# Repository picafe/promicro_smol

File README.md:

# promicro_smol

`promicro_smol` is a compact shield PCB for the nRF52840 Supermini/Pro Micro used in DIY SlimeVR trackers. It has an IMU, magnetometer, two buttons, RGB LED, battery pads and voltage reading functionality. It is designed to be compatible with existing Chrysalis enclosures (not yet verified). Production files can be found in `/pcb/production/`.

## Why I Made This

This project started as a modification of Chrysalis to support operation at 1.8V logic and to add a few features. The main changes were to make the magnetometer support 1.8V logic, switch to a MOSFET-controlled RGB LED, add a battery voltage divider for better capacity measurement, and to make sure SWD pads are accessible through a board cutout. I made these changes ensuring the board is optimized for JLCPCB economic assembly.

## Pictures

### Schematic
[View Online](https://kicanvas.org/?repo=https%3A%2F%2Fgithub.com%2Fpicafe%2Fpromicro_smol%2Fblob%2Fmain%2Fpcb%2Fpromicro_smol.kicad_sch)

### PCB
[View Online](https://kicanvas.org/?repo=https%3A%2F%2Fgithub.com%2Fpicafe%2Fpromicro_smol%2Fblob%2Fmain%2Fpcb%2Fpromicro_smol.kicad_pcb)

## Credits and Attribution

This work is derived from the [kounocom/Chrysalis](https://github.com/kounocom/Chrysalis) hardware project.

Files from `/pcb/Chrysalis-Footprints.pretty` are sourced from the Chrysalis project with and without modifications.

The upstream project is provided under CERN-OHL-S-2.0, and this repository includes the applicable license text in `LICENSE.md`.

## Bill of Materials

LCSC and other supplier pricing moves with stock, demand, quantity, and exchange rates. Treat **Unit cost** and **Total cost** as a very rough estimate. For example, the LSM6DSV has increased in price significantly in the past few months due to shortages and decreasing stock.

| Item         | Value / Part                                                                                                                                                                                                                                                                                                                          | Quantity | Unit cost | Total cost |
| ------------ | ------------------------------------------------------------------------------------------------------------------------------------------------------------------------------------------------------------------------------------------------------------------------------------------------------------------------------------- | -------- | --------- | ---------- |
| MCU module   | ProMicro nRF52840 (can be found on Aliexpress)                                                                                                                                                                                                                                                                                        | 1        | $3          | $3          |
| IMU          | [LSM6DSVQTR (C17496470)](https://www.lcsc.com/product-detail/C17496470.html)                                                                                                                                                                                                                                                             | 1        | $2.27          | $2.27          |
| Magnetometer | [QMC6309 (C5439871)](https://www.lcsc.com/product-detail/C5439871.html)                                                                                                                                                                                                                                                               | 1        | $0.36          | $0.36          |
| N-FETs       | [HL3134KT (C52204685)](https://www.lcsc.com/product-detail/C52204685.html)                                                                                                                                                                                                                                                            | 5        | $0.03          | $0.15          |
| RGB LED      | [NH-B2020RGBA-HF (C2874116)](https://www.lcsc.com/product-detail/C2874116.html)                                                                                                                                                                                                                                                       | 1        | $0.01          | $0.01          |
| Push buttons | [Tactile Button, 160gf (C318884)](https://www.lcsc.com/product-detail/C318884.html), [Tactile Button, 160gf (C720477)](https://www.lcsc.com/product-detail/C720477.html)                                                                                                                                                              | 2        | $0.07          | $0.14          |
| Resistors    | [100R (C25076)](https://www.lcsc.com/product-detail/C25076.html), [5.1k (C25905)](https://www.lcsc.com/product-detail/C25905.html), [10k (C25744)](https://www.lcsc.com/product-detail/C25744.html), [3M (C23156)](https://www.lcsc.com/product-detail/C23156.html), [4.7M (C23163)](https://www.lcsc.com/product-detail/C23163.html) | 12       | $0.01          | $0.12          |
| Capacitors   | [100nF (C307331)](https://www.lcsc.com/product-detail/C307331.html), [10nF (C15195)](https://www.lcsc.com/product-detail/C15195.html), [2.2uF (C23630)](https://www.lcsc.com/product-detail/C23630.html)                                                                                                                              | 4        | $0.01          | $0.04          |

**Approximate component cost for 1 board:** ~$6.09

**PCB fabrication and assembly:** JLCPCB, 2 boards PCBA, 0.8 mm, lead-free HASL — about US$40 (your quote will differ).

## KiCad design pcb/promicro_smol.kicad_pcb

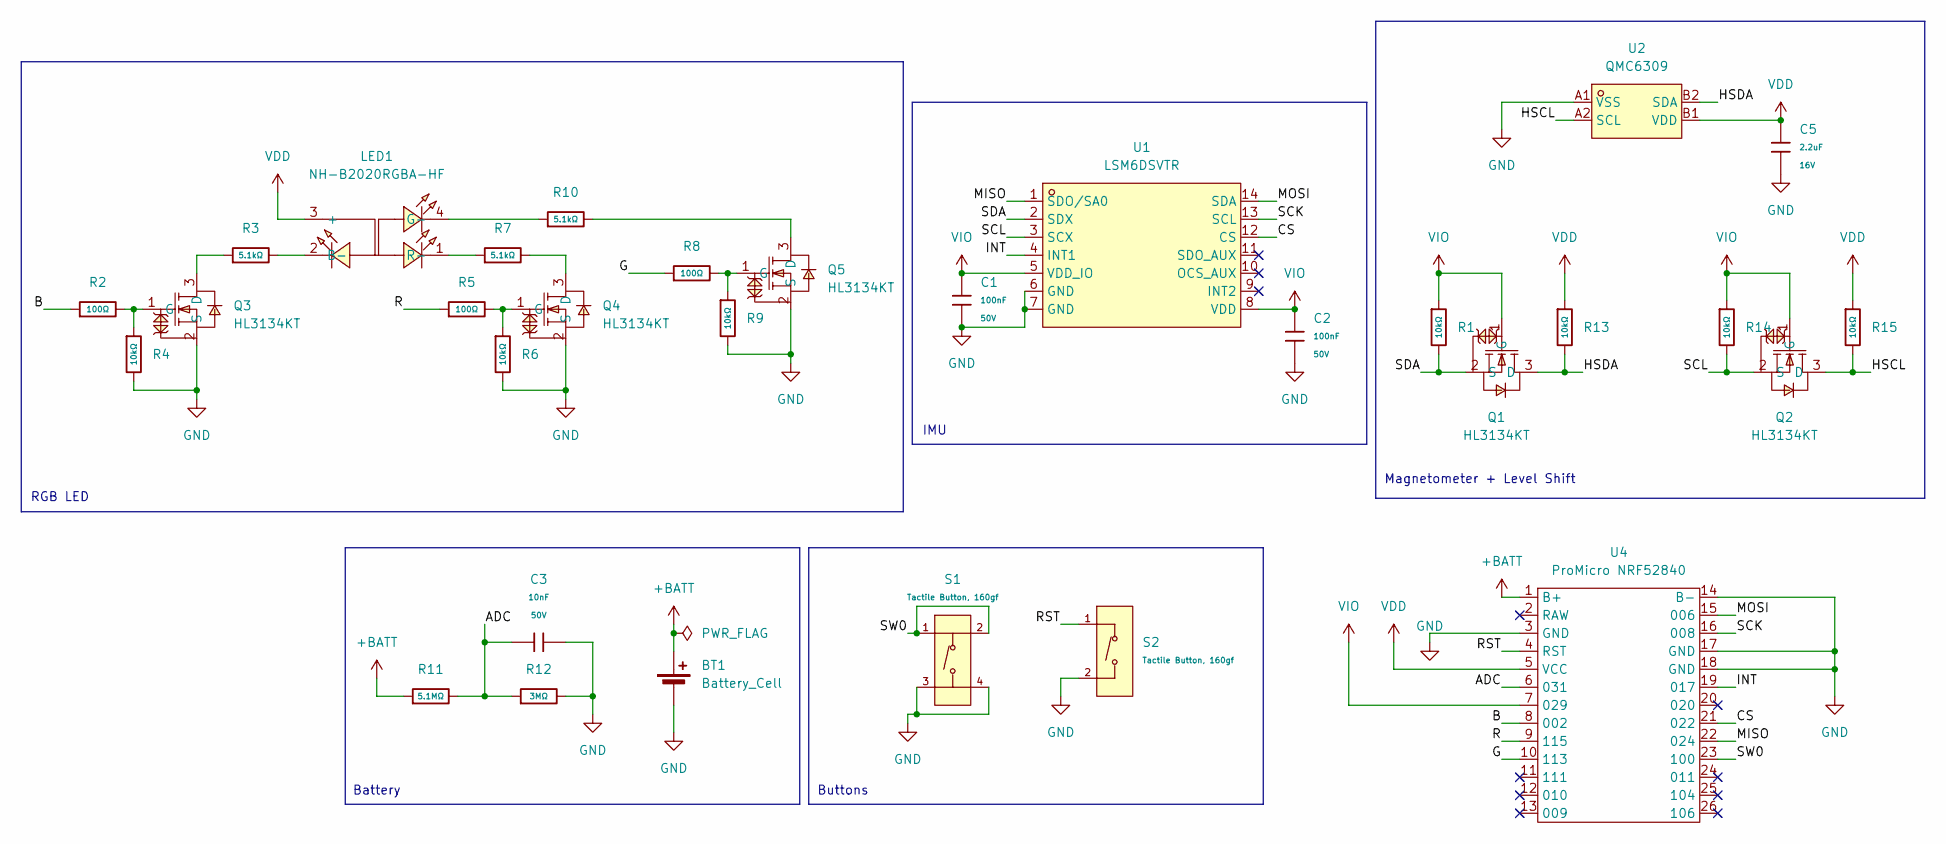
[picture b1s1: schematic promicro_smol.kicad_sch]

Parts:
BT1: Battery_Cell; Bat_Pads
C1, C2: 100nF; C_0402; Voltage Rated 50V; Tolerance ±10%; Part CL05B104KB54PNC; LCSC C307331
C3: 10nF; C_0402; Voltage Rated 50V; Tolerance ±10%; Part CL05B103KB5NNNC; LCSC C15195
C5: 2.2uF; C_0603; Voltage Rated 16V; Tolerance ±10%; Part CL10A225KO8NNNC; LCSC C23630
LED1: NH-B2020RGBA-HF; LED-ARRAY-SMD_4P-L2.1-W2.1-TL_NH-B2020RGBA; MPN NH-B2020RGBA-HF; LCSC Part C2874116
Q1, Q2, Q3, Q4, Q5: HL3134KT; SOT-523; MPN HL3134KT; LCSC Part C52204685
R1, R4, R6, R9, R13, R14, R15: 10kΩ; R_0402; Overload Voltage (Max) 50V; Tolerance ±1%; Part 0402WGF1002TCE; LCSC C25744
R2, R5, R8: 100Ω; R_0402; Overload Voltage (Max) 50V; Tolerance ±1%; Part 0402WGF1000TCE; LCSC C25076
R3, R7, R10: 5.1kΩ; R_0402; Overload Voltage (Max) 50V; Tolerance ±1%; Part 0402WGF5101TCE; LCSC C25905
R11: 5.1MΩ; R_0603; Overload Voltage (Max) 75V; Tolerance ±1%; Part 0603WAF5104T5E; LCSC C13320
R12: 3MΩ; R_0603; Overload Voltage (Max) 75V; Tolerance ±1%; Part 0603WAF3004T5E; LCSC C23156
S1: Tactile Button, 160gf; SW-SMD_4P-L5.1-W5.1-P3.70-LS6.5-TL-2; Voltage Rating (Dc) 12V; Part TS-1187A-B-A-B; LCSC C318884
S2: Tactile Button, 160gf; SW-SMD_L3.9-W3.0-P4.45; Voltage Rating (Dc) 12V; Part TS-1088-AR02016; LCSC C720477
U1: LSM6DSVTR; LGA-14_3x2.5mm_P0.5mm_LayoutBorder3x4y; MPN LSM6DSVTR; LCSC Part C5267399
U2: QMC6309; X1-WLB0808-4_L0.8-W0.8-P0.40-TL; MPN QMC6309; LCSC Part C5439871
U4: ProMicro NRF52840; Supermini nRF52840

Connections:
+BATT: BT1.1 (+), R11.1, U4.1 (B+)
/ADC: C3.1, R11.2, R12.1, U4.6 (031)
/B: R2.1, U4.8 (002)
/CS: U1.12 (CS), U4.21 (022)
/G: R8.1, U4.10 (113)
/HSCL: Q2.3 (D), R15.2, U2.A2 (SCL)
/HSDA: Q1.3 (D), R13.2, U2.B2 (SDA)
/INT: U1.4 (INT1), U4.19 (017)
/MISO: U1.1 (SDO/SA0), U4.22 (024)
/MOSI: U1.14 (SDA), U4.15 (006)
/R: R5.1, U4.9 (115)
/RST: S2.1 (A), U4.4 (RST)
/SCK: U1.13 (SCL), U4.16 (008)
/SCL: Q2.2 (S), R14.2, U1.3 (SCX)
/SDA: Q1.2 (S), R1.2, U1.2 (SDX)
/SW0: S1.1 (A), S1.2 (B), U4.23 (100)
GND: BT1.2 (-), C1.1, C2.1, C3.2, C5.2, Q3.2 (S), Q4.2 (S), Q5.2 (S), R4.2, R6.2, R9.2, R12.2, S1.3 (C), S1.4 (D), S2.2 (B), U1.6 (GND), U1.7 (GND), U2.A1 (VSS), U4.3 (GND), U4.14 (B-), U4.17 (GND), U4.18 (GND)
unnamed: LED1.2 (B-), R3.2
unnamed: LED1.4 (G-), R10.1
unnamed: LED1.1 (R-), R7.1
unnamed: Q3.3 (D), R3.1
unnamed: Q3.1 (G), R2.2, R4.1
unnamed: Q4.3 (D), R7.2
unnamed: Q4.1 (G), R5.2, R6.1
unnamed: Q5.3 (D), R10.2
unnamed: Q5.1 (G), R8.2, R9.1
VDD: C5.1, LED1.3 (+), R13.1, R15.1, U2.B1 (VDD), U4.5 (VCC)
VIO: C1.2, C2.2, Q1.1 (G), Q2.1 (G), R1.1, R14.1, U1.5 (VDD_IO), U1.8 (VDD), U4.7 (029)

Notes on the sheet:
Battery
Buttons
Magnetometer + Level Shift
IMU
RGB LED

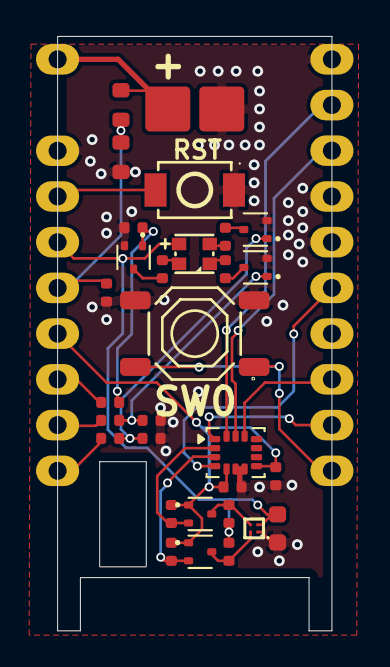
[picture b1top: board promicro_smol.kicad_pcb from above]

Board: 2 copper layers, 15.2 x 33.0 mm, 31 parts (0 on the bottom side), 28 nets.

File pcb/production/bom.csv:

Designator,Footprint,Quantity,Value,LCSC Part #
"C1, C2",C_0402,2,100nF,C307331
C3,C_0402,1,10nF,C15195
C5,C_0603,1,2.2uF,C23630
LED1,LED-ARRAY-SMD_4P-L2.1-W2.1-TL_NH-B2020RGBA,1,NH-B2020RGBA-HF,C2874116
"Q1, Q2, Q3, Q4, Q5",SOT-523,5,HL3134KT,C52204685
"R1, R13, R14, R15, R4, R6, R9",R_0402,7,10kΩ,C25744
"R10, R3, R7",R_0402,3,5.1kΩ,C25905
R11,R_0603,1,5.1MΩ,C13320
R12,R_0603,1,3MΩ,C23156
"R2, R5, R8",R_0402,3,100Ω,C25076
S1,SW-SMD_4P-L5.1-W5.1-P3.70-LS6.5-TL-2,1,"Tactile Button, 160gf",C318884
S2,SW-SMD_L3.9-W3.0-P4.45,1,"Tactile Button, 160gf",C720477
U1,LGA-14_3x2.5mm_P0.5mm_LayoutBorder3x4y,1,LSM6DSVTR,C5267399
U2,X1-WLB0808-4_L0.8-W0.8-P0.40-TL,1,QMC6309,C5439871
U4,Supermini nRF52840,1,ProMicro NRF52840,

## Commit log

2026-05-06 init
2026-05-06 feat: readme
2026-05-06 fix: readme
2026-05-10 fix: filenames, minor routing
2026-05-10 feat: restructure + readme + gerbers
2026-05-10 spacing
2026-05-11 feat: update readme
2026-05-12 feat: routing + ADC res
2026-05-12 fix: weird gnd pour
